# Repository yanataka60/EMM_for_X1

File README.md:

# EMMボード for X1

　X1、X1turbo用の512K S-RAM EMMボードを作ってみました。

　特徴としては、

　1)I/Oポートは、SHARP CZ-8EM互換なのでそのままCZ-8EM(320K EMM)として使えます。

　2)CR-2032のバックアップにより電源を切ってもメモリ内容が保持されます。(Rev1.8のバックアップ期間は計算上数年は大丈夫です。)

　3)スイッチにより書込み禁止にできます。

　4)I/Oポートから直接EMMを読み書きすれば512K外部RAMとして使えます。

　5)X1_SDと併用すれば512KまるごとSDカードからLOAD、SAVEが可能です。

　6)ジャンパによりEMM0～EMM3のいずれかに設定して使えます。

　7)おまけでアドレスカウンタリセットを付けました。

　なお、X1本体の通常の電源ON/OFFでの正常動作は確認していますが、電源ON/OFFを瞬間的に繰り返すような無理な使い方をするとEMMのバックアップが正常に動作しないことがあります。電源ON/OFFを瞬間的に繰り返すと電源ユニットにもダメージが及ぶこともあるので電源ON/OFFは間をおいて行ってください。

## 回路図

[回路図](https://github.com/yanataka60/EMM_for_X1/blob/main/Kicad/X1_EMM.pdf)

## 部品表
|番号|品名|数量|備考|
| ------------ | ------------ | ------------ | ------------ |
|C1-C16,C19|積層セラミックコンデンサ 0.1uF|17||
|C17|積層セラミックコンデンサ 220pF|1||
|C18|電解コンデンサ 100uF|1||
|D1-D2|ダイオード 1N4148|2|1S4から1N4148に変更|
|Q1|FET 2N7000|1||
|R1|カーボン抵抗 100Ω|1||
|R2|カーボン抵抗 1k|1||
|R3|カーボン抵抗 10k|1||
|S1,S2|3Pスライドスイッチ又は1x3ピンヘッダとジャンパーピン|1|秋月電子通商 SS12D01G4又はPH-1X3SG,MJ-254-6BK等|
|S3|3Pスライドスイッチ|1|秋月電子通商 SS12D01G4等|
|U1,U2,U17|74LS04|3|樫木総業等|
|U3,U4|74LS30|2|樫木総業等|
|U5|74LS14|1|樫木総業等|
|U6,U16|74LS245|2|樫木総業等|
|U7-U11|74LS193|5|樫木総業等|
|U12,U13|74LS138|2|樫木総業等|
|U14|SRAM HM628512|1|注1)|
|U15|74LS11|1|樫木総業等|
|BT1|ボタン電池基板取付用ホルダー CR2032用(小型タイプ)|1|秋月電子通商 CH25-2032LFなど|

注1)DIPで設計しています。SOPを入手した場合にはこちらの変換基板を使うことで装着できます。

https://github.com/yanataka60/SOPtoDIP32

## I/Oポート
### EMM0
ジャンパピンA3、A2とも0の位置にします。

|アドレス|R/W|説明|
| ------------ | ------------ | ------------ |
|0D00h|R|アドレスカウンタリセット|
|0D00h|W|アドレスカウンタ Bit[7:0]|
|0D01h|W|アドレスカウンタ Bit[15:8]|
|0D02h|W|アドレスカウンタ Bit[18:16]|
|0D03h|R|データ読み出し:アドレスカウンタ+1|
|0D03h|W|データ書き込み:アドレスカウンタ+1|
### EMM1
ジャンパピンA3を0、A2を1の位置にします。

|アドレス|R/W|説明|
| ------------ | ------------ | ------------ |
|0D04h|R|アドレスカウンタリセット|
|0D04h|W|アドレスカウンタ Bit[7:0]|
|0D05h|W|アドレスカウンタ Bit[15:8]|
|0D06h|W|アドレスカウンタ Bit[18:16]|
|0D07h|R|データ読み出し:アドレスカウンタ+1|
|0D07h|W|データ書き込み:アドレスカウンタ+1|
### EMM2
ジャンパピンA3を1、A2を0の位置にします。

|アドレス|R/W|説明|
| ------------ | ------------ | ------------ |
|0D08h|R|アドレスカウンタリセット|
|0D08h|W|アドレスカウンタ Bit[7:0]|
|0D09h|W|アドレスカウンタ Bit[15:8]|
|0D0Ah|W|アドレスカウンタ Bit[18:16]|
|0D0Bh|R|データ読み出し:アドレスカウンタ+1|
|0D0Bh|W|データ書き込み:アドレスカウンタ+1|
### EMM3
ジャンパピンA3、A2とも1の位置にします。

|アドレス|R/W|説明|
| ------------ | ------------ | ------------ |
|0D0Ch|R|アドレスカウンタリセット|
|0D0Ch|W|アドレスカウンタ Bit[7:0]|
|0D0Dh|W|アドレスカウンタ Bit[15:8]|
|0D0Eh|W|アドレスカウンタ Bit[18:16]|
|0D0Fh|R|データ読み出し:アドレスカウンタ+1|
|0D0Fh|W|データ書き込み:アドレスカウンタ+1|

## SAMPLEプログラム
　SAMPLEフォルダ内にEMMMENU、EMMCHECK、EMMTESTを置きました。

　使い方については、フォルダ内のREADME.mdを参照してください。

## EMMからの起動
　せっかくバッテリーバックアップに対応させたのでX1_SDの起動時にEMMから起動できるようにしてみました。

　X1_SDのROMをEMM対応BOOT LOADERに書き換える必要があります。

　X1_SDの「EMMボード for X1からの起動」を参照してください。

　https://github.com/yanataka60/X1_SD?tab=readme-ov-file#emm%E3%83%9C%E3%83%BC%E3%83%89-for-x1%E3%81%8B%E3%82%89%E3%81%AE%E8%B5%B7%E5%8B%95

## 初期基板をバッテリーバックアップ対応とするには
#### 2026.2.16 Rev1.8基板ではバックアップ時間が飛躍的に増加し、ICに負荷をかけない回路となりました。バッテリーバックアップを使うなら出来ればRev1.8基板に更新してください。

　以下に示すパターンカット、ジャンパ、追加部品(74LS04×1個、抵抗10k×1本、ダイオード1S4×1本)で改造することで初期基板をバッテリーバックアップ対応とすることが可能です。

　部品を外すことなくパターンカットが可能ですが、ボード上に余っているゲートが無いため74LS04を1個追加しています。

### パターンカット個所
　HM628512の29PinとU15 74LS11 2Pinとの接続をカットします。

　HM628512の22、24Pin、R2 10Kとの接続点とU13 74LS138 5Pinとの接続をカットします。

　HM628512の22、24Pin、R2 10Kとの接続点とU12 74LS138 4Pinとの接続をカットします。

部品面全体

ハンダ面全体

### ジャンパ個所
　U12 74LS138 4PinとU13 74LS138 5Pin

　U13 74LS138 5Pinと追加74LS04 3Pin

　追加74LS04 4Pinと5Pin

　追加74LS04 6PinとU14 HM628512 24Pin(画像ではR2 10KのU14 HM628512 24Pinと接続されている方)

　U13 74LS138 12Pinと追加74LS04 11Pin

　追加74LS04 10Pinと9Pin

　追加74LS04 8Pinと追加ダイオード 1S4 アノード

　追加ダイオード 1S4 カソードとU14 HM628512 29Pin

　U14 HM628512 29Pinと追加抵抗 10KとU14 HM628512 32Pin

　U13 74LS138 8Pin(GND)と追加74LS04 7Pin(GND)

　U13 74LS138 16Pin(5V)と追加74LS04 14Pin(5V)

ハンダ面全体

ハンダ面拡大1

ハンダ面拡大2

部品面全体

## 追記
2025.12.22 SAMPLEプログラムを追加しました。

2025.12.28 バッテリーバックアップしていてもメモリ内容が変わってしまう症状が時々発生しています。原因と対策を検討中です。

2026.1.1 簡単な修正では症状を抑えることが出来ないのでこのバージョンではバッテリーバックアップは断念し、対策を練りなおします。

2026.1.23 バッテリーバックアップ正常版(Rev1.5)に更新。初期基板をバッテリーバックアップ対応とするための改修方法を記述。

2026.1.23 バックアップ期間について追記。

2026.1.24 HM628512の書き込み時WE信号が瞬間的に5.9Vほどの電圧が掛かることを記述。すーぱーたーぼさんご指摘ありがとうございました。

2026.1.25 D1,D2を1S4から1N4148に変更。AIGOU Yoshiakiさんアドバイスありがとうございました。

2026.2.16 すーぱーたーぼさんに提案していただいていたn-FETを用いたバッテリーバックアップ回路を採用しました。すーぱーたーぼさんアドバイスありがとうございました。

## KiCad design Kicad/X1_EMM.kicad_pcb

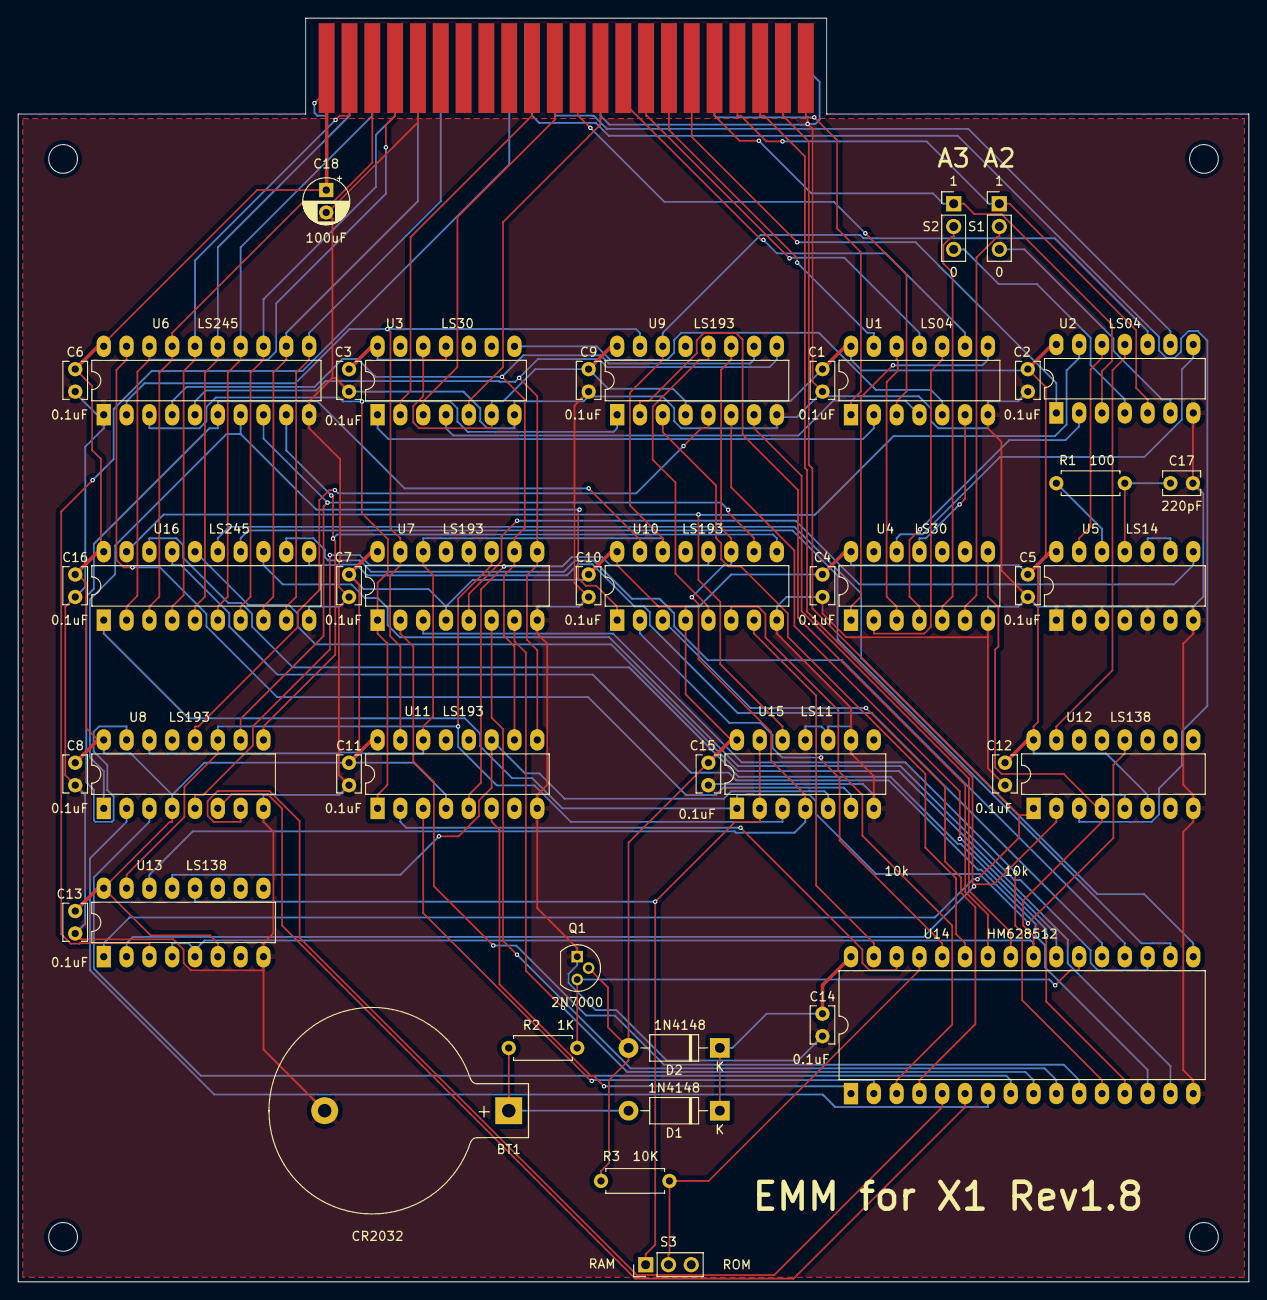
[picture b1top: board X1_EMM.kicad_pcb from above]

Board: 2 copper layers, 137.0 x 140.7 mm, 49 parts (0 on the bottom side), 97 nets.

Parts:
BT1: Battery_Cell; BatteryHolder_Keystone_103_1x20mm
C1, C2, C3, C4, C5, C6, C7, C8, C9, C10, C11, C12, C13, C14, C15, C16: 0.1uF; C_Rect_L4.0mm_W2.5mm_P2.50mm
C17: 220pF; C_Rect_L4.0mm_W2.5mm_P2.50mm
C18: 100uF; CP_Radial_D5.0mm_P2.50mm
D1, D2: 1N4148; D_DO-41_SOD81_P10.16mm_Horizontal
J1: for Card-Slot; BUS_MZ2000
MH1, MH2, MH3, MH4: MountingHole_3.2mm_M3
Q1: 2N7000; TO-92
R1: 100; R_Axial_DIN0207_L6.3mm_D2.5mm_P7.62mm_Horizontal
R2: 1K; R_Axial_DIN0207_L6.3mm_D2.5mm_P7.62mm_Horizontal
R3: 10K; R_Axial_DIN0207_L6.3mm_D2.5mm_P7.62mm_Horizontal
S1: A2_select; PinHeader_1x03_P2.54mm_Vertical
S2: A3_select; PinHeader_1x03_P2.54mm_Vertical
S3: SLIDE_SWITCH_3P; PinHeader_1x03_P2.54mm_Vertical
U1, U2: 74LS04; DIP-14_W7.62mm_LongPads
U3, U4: 74LS30; DIP-14_W7.62mm_LongPads
U5: 74LS14; DIP-14_W7.62mm_LongPads
U6, U16: 74LS245; DIP-20_W7.62mm_LongPads
U7, U8, U9, U10, U11: 74LS193; DIP-16_W7.62mm_LongPads
U12, U13: 74LS138; DIP-16_W7.62mm_LongPads
U14: HM628512LFP-5; DIP-32_W15.24mm_LongPads
U15: 74LS11; DIP-14_W7.62mm_LongPads

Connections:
+5V: C1.1, C2.1, C3.1, C4.1, C5.1, C6.1, C7.1, C8.1, C9.1, C10.1, C11.1, C12.1, C13.1, C15.1, C16.1, C18.1, D2.2, J1.a1, J1.b1, Q1.2, R3.2, U1.14, U2.14, U3.6, U3.11, U3.12, U3.14, U4.14, U5.14, U6.20, U7.4, U7.16, U8.4, U8.16, U9.4, U9.16, U10.4, U10.16, U11.4, U11.16, U12.6, U12.16, U13.6, U13.16, U15.14, U16.20
/A0: J1.a21, U12.1, U13.1
/A1: J1.a20, U12.2, U13.2
/A2: J1.a19, S1.1, U2.5
/A3: J1.a18, S2.1, U2.3
/A4: J1.a17, U2.1
/A5: J1.a16, U1.13
/A6: J1.a15, U1.11
/A7: J1.a14, U1.9
/A8: J1.a13, U3.5
/A9: J1.a12, U1.3
/A10: J1.a11, U3.3
/A11: J1.a10, U3.2
/D0: J1.a4, U6.18, U16.2
/D1: J1.a3, U6.17, U16.3
/D2: J1.a2, U6.16, U16.4
/D3: J1.b2, U6.15, U16.5
/D4: J1.b3, U6.14, U16.6
/D5: J1.b4, U6.13, U16.7
/D6: J1.b5, U6.12, U16.8
/D7: J1.b6, U6.11, U16.9
/x0_RD: U2.11, U12.15
/x0_WR: U7.11, U8.11, U13.15, U15.3
/x1_WR: U9.11, U10.11, U13.14, U15.4
/x2_WR: U11.11, U13.13, U15.5
/x3_RD: U12.12, U15.1, U16.1
/x3_WR: S3.1, U13.12, U15.2, U15.13
/~EXIO: J1.b18, U1.1
/~IOREQ: J1.b11, U2.9
/~RD: J1.b10, U12.3
/~WR: J1.b9, U13.3
GND: BT1.2, C1.2, C2.2, C3.2, C4.2, C5.2, C6.2, C7.2, C8.2, C9.2, C10.2, C11.2, C12.2, C13.2, C14.2, C15.2, C16.2, C17.2, C18.2, J1.a5, J1.a22, J1.b13, J1.b22, Q1.1, U1.7, U2.7, U3.7, U4.7, U5.1, U5.3, U5.5, U5.7, U6.1, U6.10, U7.8, U8.8, U9.8, U10.8, U11.8, U12.8, U13.8, U14.16, U15.7, U15.9, U15.10, U15.11, U16.10
unnamed: BT1.1, D1.2, R2.2
unnamed: C14.1, D1.1, D2.1, U14.32
unnamed: C17.1, R1.2, U5.11
unnamed: Q1.3, R2.1, U14.22
unnamed: R1.1, U5.12
unnamed: R3.1, S3.2, U14.29
unnamed: S1.2, U4.6
unnamed: S1.3, U2.6
unnamed: S2.2, U4.5
unnamed: S2.3, U2.4
unnamed: U1.2, U3.1
unnamed: U1.4, U3.4
unnamed: U1.5, U3.8
unnamed: U1.6, U4.11
unnamed: U1.8, U4.1
unnamed: U1.10, U4.2
unnamed: U1.12, U4.3
unnamed: U2.2, U4.4
unnamed: U2.8, U4.12
unnamed: U2.12, U5.13
unnamed: U5.8, U7.5
unnamed: U5.9, U5.10
unnamed: U7.12, U8.5
unnamed: U8.12, U9.5
unnamed: U6.7, U8.1, U10.1
unnamed: U10.2, U14.28
unnamed: U10.3, U14.4
unnamed: U9.12, U10.5
unnamed: U10.6, U14.3
unnamed: U10.7, U14.31
unnamed: U6.9, U8.9, U10.9
unnamed: U6.8, U8.10, U10.10
unnamed: U10.12, U11.5
unnamed: U2.10, U7.14, U8.14, U9.14, U10.14, U11.14
unnamed: U6.6, U8.15, U10.15
unnamed: U6.3, U7.1, U9.1, U11.1
unnamed: U11.2, U14.30
unnamed: U11.3, U14.2
unnamed: U11.6, U14.1
unnamed: U6.5, U7.9, U9.9, U11.9
unnamed: U6.4, U7.10, U9.10, U11.10
unnamed: U6.2, U7.15, U9.15, U11.15
unnamed: U4.8, U12.4, U12.5, U13.4, U13.5, U14.24
unnamed: U8.7, U14.5
unnamed: U8.6, U14.6
unnamed: U8.2, U14.7
unnamed: U8.3, U14.8
unnamed: U7.7, U14.9
unnamed: U7.6, U14.10
unnamed: U7.2, U14.11
unnamed: U7.3, U14.12
unnamed: U14.13, U16.18
unnamed: U14.14, U16.17
unnamed: U14.15, U16.16
unnamed: U14.17, U16.15
unnamed: U14.18, U16.14
unnamed: U14.19, U16.13
unnamed: U14.20, U16.12
unnamed: U14.21, U16.11
unnamed: U9.6, U14.23
unnamed: U9.7, U14.25
unnamed: U9.2, U14.26
unnamed: U9.3, U14.27
unnamed: U6.19, U15.6
unnamed: U2.13, U15.12, U16.19
